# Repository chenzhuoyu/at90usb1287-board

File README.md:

# at90usb1287-board
AT90USB1286/1287 breakout board

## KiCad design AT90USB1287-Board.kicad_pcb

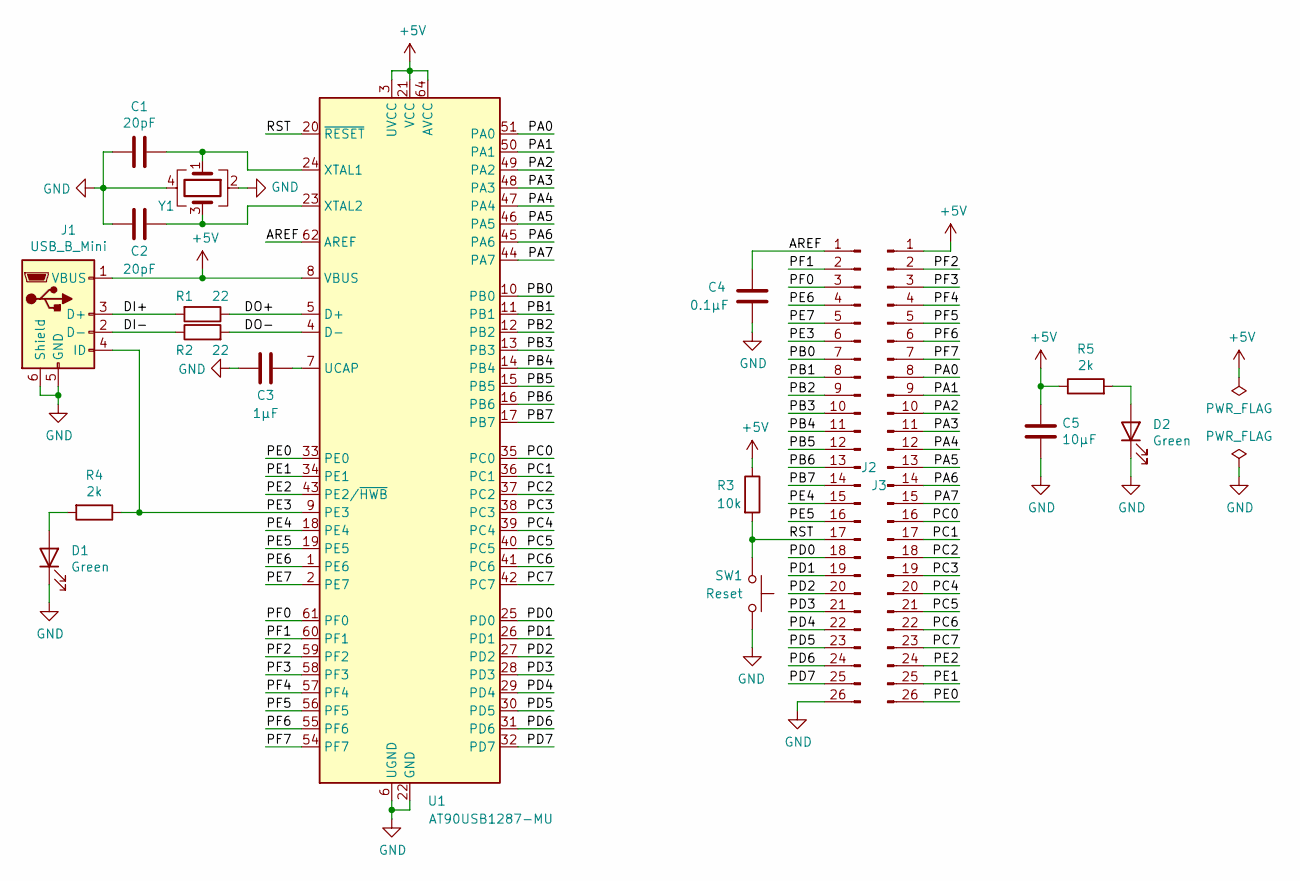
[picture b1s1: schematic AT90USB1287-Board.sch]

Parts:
C1, C2: 20pF; C_0402_1005Metric
C3: 1μF; C_0402_1005Metric
C4: 0.1μF; C_0402_1005Metric
C5: 10μF; C_1206_3216Metric
D1, D2: Green; LED_0805_2012Metric
J1: USB_B_Mini; USB_Mini-B_Wuerth_65100516121_Horizontal
J2, J3: Conn_01x26_Male; PinHeader_1x26_P2.54mm_Vertical
R1, R2: 22; R_0402_1005Metric
R3: 10k; R_0402_1005Metric
R4, R5: 2k; R_0402_1005Metric
SW1: Reset; SW_SPST_EVQPE1
U1: AT90USB1287-MU; QFN-64-1EP_9x9mm_P0.5mm_EP7.5x7.5mm
Y1: Crystal_GND24; Crystal_SMD_3225-4Pin_3.2x2.5mm

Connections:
+5V: C5.1, J1.1 (VBUS), J3.1, R3.1, R5.1, U1.3 (UVCC), U1.8 (VBUS), U1.21 (VCC), U1.52 (VCC), U1.64 (AVCC)
/AREF: C4.1, J2.1, U1.62 (AREF)
/DI+: J1.3 (D+), R1.2
/DI-: J1.2 (D-), R2.1
/DO+: R1.1, U1.5 (D+)
/DO-: R2.2, U1.4 (D-)
/PA0: J3.8, U1.51 (PA0)
/PA1: J3.9, U1.50 (PA1)
/PA2: J3.10, U1.49 (PA2)
/PA3: J3.11, U1.48 (PA3)
/PA4: J3.12, U1.47 (PA4)
/PA5: J3.13, U1.46 (PA5)
/PA6: J3.14, U1.45 (PA6)
/PA7: J3.15, U1.44 (PA7)
/PB0: J2.7, U1.10 (PB0)
/PB1: J2.8, U1.11 (PB1)
/PB2: J2.9, U1.12 (PB2)
/PB3: J2.10, U1.13 (PB3)
/PB4: J2.11, U1.14 (PB4)
/PB5: J2.12, U1.15 (PB5)
/PB6: J2.13, U1.16 (PB6)
/PB7: J2.14, U1.17 (PB7)
/PC0: J3.16, U1.35 (PC0)
/PC1: J3.17, U1.36 (PC1)
/PC2: J3.18, U1.37 (PC2)
/PC3: J3.19, U1.38 (PC3)
/PC4: J3.20, U1.39 (PC4)
/PC5: J3.21, U1.40 (PC5)
/PC6: J3.22, U1.41 (PC6)
/PC7: J3.23, U1.42 (PC7)
/PD0: J2.18, U1.25 (PD0)
/PD1: J2.19, U1.26 (PD1)
/PD2: J2.20, U1.27 (PD2)
/PD3: J2.21, U1.28 (PD3)
/PD4: J2.22, U1.29 (PD4)
/PD5: J2.23, U1.30 (PD5)
/PD6: J2.24, U1.31 (PD6)
/PD7: J2.25, U1.32 (PD7)
/PE0: J3.26, U1.33 (PE0)
/PE1: J3.25, U1.34 (PE1)
/PE2: J3.24, U1.43 (PE2/~HWB)
/PE3: J1.4 (ID), J2.6, R4.1, U1.9 (PE3)
/PE4: J2.15, U1.18 (PE4)
/PE5: J2.16, U1.19 (PE5)
/PE6: J2.4, U1.1 (PE6)
/PE7: J2.5, U1.2 (PE7)
/PF0: J2.3, U1.61 (PF0)
/PF1: J2.2, U1.60 (PF1)
/PF2: J3.2, U1.59 (PF2)
/PF3: J3.3, U1.58 (PF3)
/PF4: J3.4, U1.57 (PF4)
/PF5: J3.5, U1.56 (PF5)
/PF6: J3.6, U1.55 (PF6)
/PF7: J3.7, U1.54 (PF7)
/RST: J2.17, R3.2, SW1.2, U1.20 (~RESET)
GND: C1.2, C2.2, C3.2, C4.2, C5.2, D1.1 (K), D2.1 (K), J1.5 (GND), J1.6 (Shield), J2.26, SW1.1, U1.6 (UGND), U1.22 (GND), U1.53 (GND), U1.63 (GND), U1.65 (GND), Y1.2, Y1.4
unnamed: C1.1, U1.24 (XTAL1), Y1.1
unnamed: C2.1, U1.23 (XTAL2), Y1.3
unnamed: C3.1, U1.7 (UCAP)
unnamed: D1.2 (A), R4.2
unnamed: D2.2 (A), R5.2

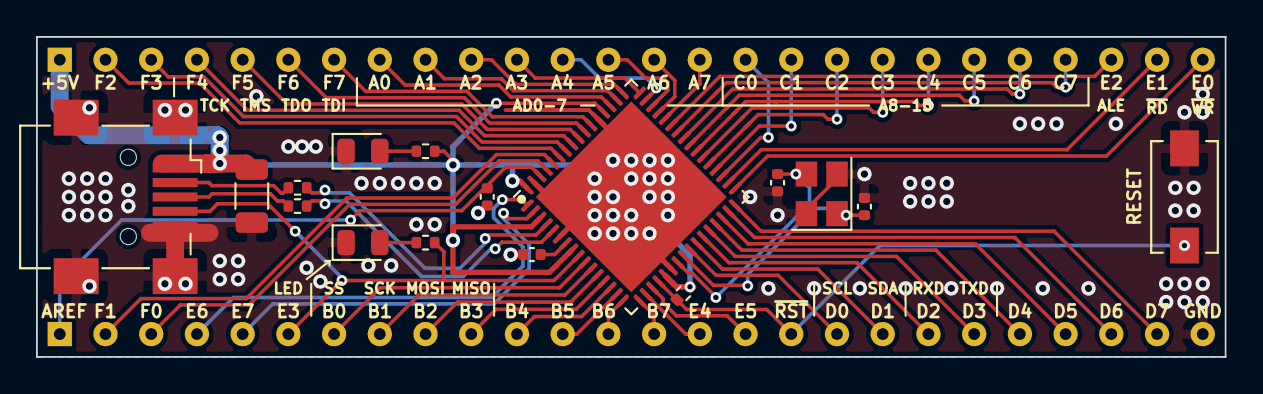
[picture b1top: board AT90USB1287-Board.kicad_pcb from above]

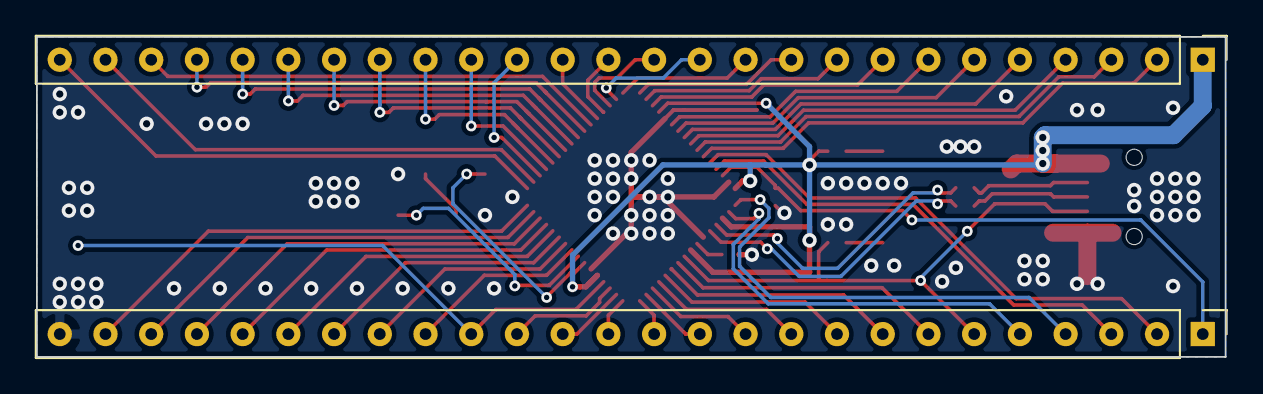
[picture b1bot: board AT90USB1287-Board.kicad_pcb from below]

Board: 2 copper layers, 66.0 x 17.8 mm, 18 parts (2 on the bottom side), 61 nets.

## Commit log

2021-09-16 feat: board version 2
